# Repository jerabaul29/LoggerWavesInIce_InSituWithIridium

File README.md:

### NOTE - the content of this repository is kept available for archive, but we have a better instrument design released in 2021, see: https://github.com/jerabaul29/OpenMetBuoy-v2021a .

# Logger waves in ice with solar panel and Iridium communications

This is the repository for the 'waves in ice' instrument developed in this work:

```
An open source, versatile, affordable waves in ice instrument for scientific measurements in the Polar Regions
Jean Rabault, Graig Sutherland, Olav Gundersen, Atle Jensen, Aleksey Marchenko, Øyvind Breivik
```

https://www.sciencedirect.com/science/article/pii/S0165232X19300230

(preprint available here: https://arxiv.org/pdf/1901.02410.pdf ).

## Content of the repository

- **PCB_electronics**: details about the electronics boards.
- **DevelopmentCode**: code for the different components of the loggers.
- **ElectronicsList**: some bookkeeping of which components I need to buy to assemble. May be outdated.
- **SeedOPL**: the Seeed studios standard library. Could be used for putting the components on PCB from factory, not used now.

Quite a lot of cleaning and more detailed readmes is needed. This will happen as time goes and new series of instruments get built. If you have any questions, open an issue and / or feel free to contact me at ```jean.rblt@gmail.com```.

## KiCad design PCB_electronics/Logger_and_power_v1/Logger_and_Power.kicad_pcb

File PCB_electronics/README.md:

PCB files. The software used for developing this is the Open Source KiCAD.

Most advanced PCB is in **Logger_and_power_v1**.

Production was made through Seeed.

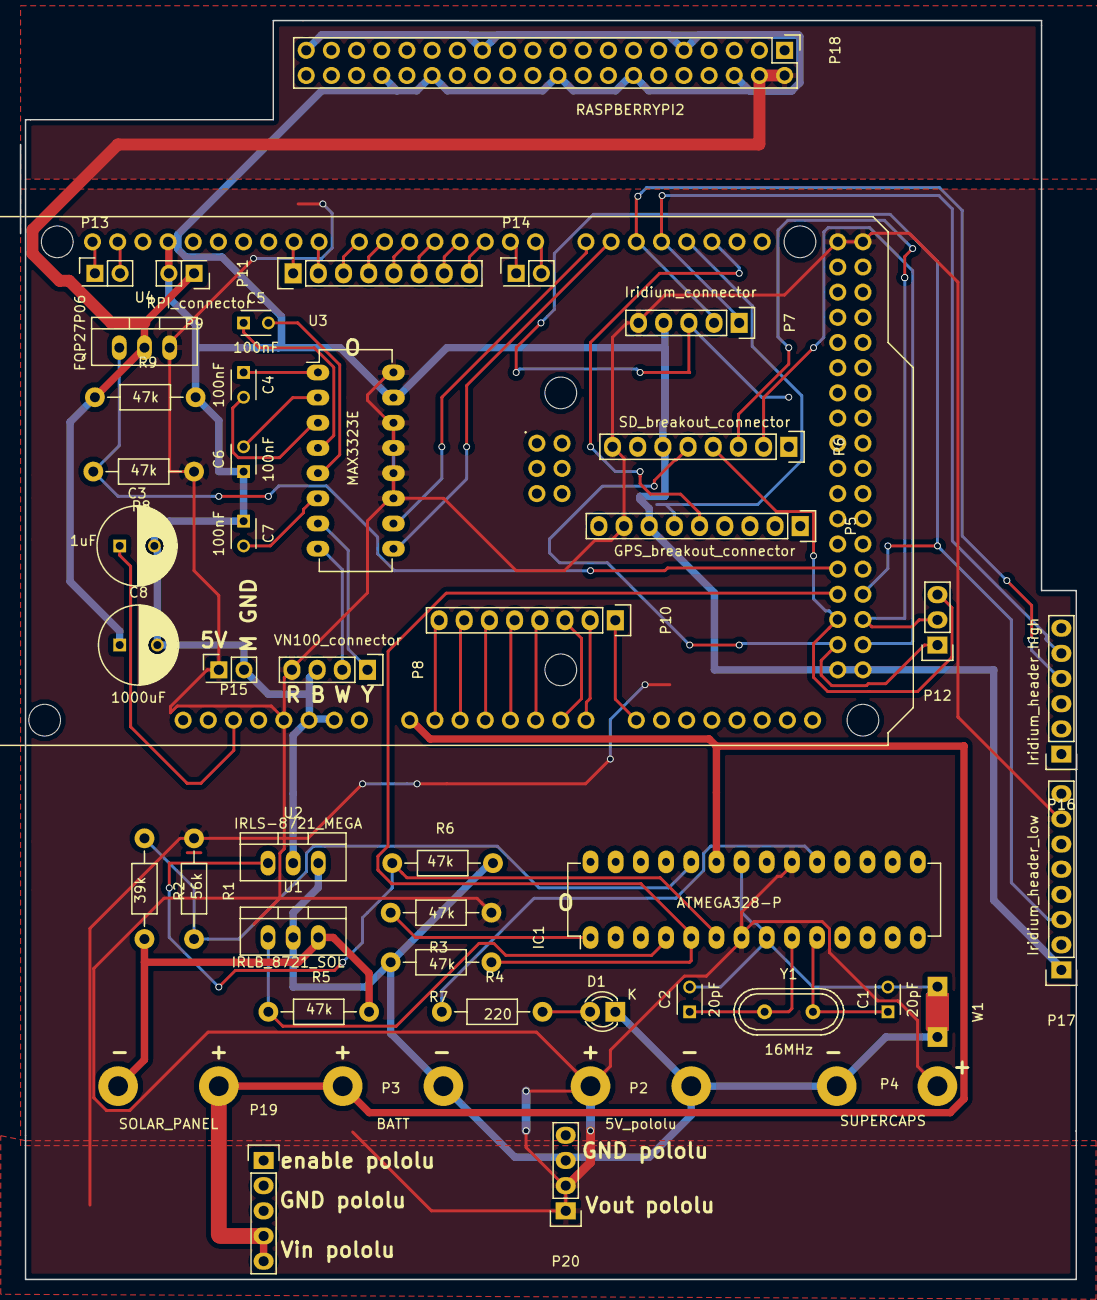
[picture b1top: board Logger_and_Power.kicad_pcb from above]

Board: 2 copper layers, 106.5 x 127.0 mm, 46 parts (1 on the bottom side), 57 nets.

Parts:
C1, C2: 20pF; C_Disc_D3_P2.5
C3: 1uF; C_Radial_D8_L11.5_P3.5
C4, C5, C6, C7: 100nF; C_Disc_D3_P2.5
C8: 1000uF; C_Radial_D8_L13_P3.8
D1: LED; LED-3MM
IC1: ATMEGA328-P; DIP-28_W7.62mm_LongPads
P1: SOLAR_PANEL; WireConnection_2.00mmDrill
P2: 5V_pololu; WireConnection_2.00mmDrill
P3: BATT; WireConnection_2.00mmDrill
P4: SUPERCAPS; WireConnection_2.00mmDrill
P5: GPS_breakout_connector; Pin_Header_Straight_1x09
P6: SD_breakout_connector; Pin_Header_Straight_1x08
P7: Iridium_connector; Pin_Header_Straight_1x05
P8: VN100_connector; Pin_Header_Straight_1x04
P9: RPI_connector; Pin_Header_Straight_2x01
P10, P11: CONN_01X08; Pin_Header_Straight_1x08
P12: CONN_01X03; Pin_Header_Straight_1x03
P13, P14, P15: CONN_01X02; Pin_Header_Straight_2x01
P16: Iridium_header_high; Pin_Header_Straight_1x06
P17: Iridium_header_low; Pin_Header_Straight_1x08
P18: RASPBERRYPI2; Pin_Header_Straight_2x20
P19: header_pololu_in; Pin_Header_Straight_1x05
P20: header_pololu_out; Pin_Header_Straight_1x04
R1: 56k; Resistor_Horizontal_RM10mm
R2: 39k; Resistor_Horizontal_RM10mm
R3, R5, R6, R7, R8, R9: 47k; Resistor_Horizontal_RM10mm
R4: 220; Resistor_Horizontal_RM10mm
U1: IRLB_8721_SOL; TO-220_Neutral123_Vertical
U2: IRLS-8721_MEGA; TO-220_Neutral123_Vertical
U3: MAX3323E; DIP-16_W7.62mm_LongPads
U4: FQP27P06; TO-220_Neutral123_Vertical
W1: NET-TIE; NetTie-I_Connected
XA1: Arduino_Mega2560_Shield
Y1: 16MHz; Crystal_HC49-U_Vertical

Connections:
+5V: IC1.7, IC1.20, P2.1, P4.1, P5.8, P6.8, P7.5, P8.4, P15.1, P17.7, P20.1, P20.2, R1.1, R3.1, R8.1, U3.11, U3.12, U3.13, U3.14, U3.16, U4.3, XA1.5V1, XA1.5V3, XA1.5V4
/Logger_part/ANALOG_1: P10.1, XA1.A8
/Logger_part/ANALOG_2: P10.2, XA1.A7
/Logger_part/ANALOG_3: P10.3, XA1.A6
/Logger_part/ANALOG_4: P10.4, XA1.A5
/Logger_part/ANALOG_5: P10.5, XA1.A4
/Logger_part/ANALOG_6: P10.6, XA1.A3
/Logger_part/ANALOG_7: P10.7, XA1.A2
/Logger_part/ANALOG_8: P10.8, XA1.A1
/Logger_part/DGTL_1: P11.1, XA1.D9
/Logger_part/DGTL_2: P11.2, XA1.D8
/Logger_part/DGTL_3: P11.3, XA1.D7
/Logger_part/DGTL_4: P11.4, XA1.D6
/Logger_part/DGTL_5: P11.5, XA1.D5
/Logger_part/DGTL_6: P11.6, XA1.D4
/Logger_part/DGTL_7: P11.7, XA1.D3
/Logger_part/DGTL_8: P11.8, XA1.D2
/Logger_part/IRD_ON_OFF: P7.3, P17.3, XA1.D49
/Logger_part/IRD_RXC: P7.1, P16.5, XA1.D17
/Logger_part/IRD_TXD: P7.2, P16.4, XA1.D16
/Logger_part/MEGA_RX_1: P5.5, XA1.D19
/Logger_part/MEGA_TX_1: P5.6, XA1.D18
/Logger_part/MISO: P6.4, P12.3, XA1.D50
/Logger_part/MOSI: P6.3, P12.2, XA1.D51
/Logger_part/RPI_control: R8.2, U4.1, XA1.D46
/Logger_part/RPI_header/RPI_power_5V: C8.1, P9.1, P18.2, P18.4, R9.1, U4.2
/Logger_part/RX0: P14.2, XA1.D0
/Logger_part/RX3: U3.9, XA1.D15
/Logger_part/SCK: P6.5, P12.1, XA1.D52
/Logger_part/SCL: P13.1, XA1.SCL
/Logger_part/SDA: P13.2, XA1.SDA
/Logger_part/SS: P6.2, XA1.D53
/Logger_part/TX0: P14.1, XA1.D1
/Logger_part/TX3: U3.10, XA1.D14
/Logger_part/VN_WHITE: P8.2, U3.8
/Logger_part/VN_YELLOW: P8.1, U3.7
/Power_part/A1: IC1.24, R1.2, R2.1
/Power_part/Batt_plus: IC1.23, P1.1, P3.1, P19.4, P19.5, XA1.A0
/Power_part/D3: IC1.4, R5.1, U1.1
/Power_part/D5: IC1.6, R6.1, U2.1
/Power_part/Feedback_Mega: IC1.5, R7.1, XA1.D48
/Power_part/MSFT_SOLAR_S: P1.2, R2.2, R5.2, U1.3
/Power_part/Mega_ground: C3.2, C6.1, C7.1, C8.2, P5.7, P6.6, P7.4, P8.3, P9.2, P15.2, P17.1, P18.6, P18.9, P18.14, P18.20, P18.25, P18.30, P18.34, P18.39, R9.2, U2.2, U3.15, XA1.GND1, XA1.GND2, XA1.GND3, XA1.GND5, XA1.GND6
/Power_part/Ref_gnd: C1.2, C2.2, IC1.8, IC1.22, W1.2
GND: D1.1, P2.2, P3.2, P4.2, P19.2, P19.3, P20.3, P20.4, R6.2, R7.2, U1.2, U2.3, W1.1
unnamed: C1.1, IC1.10, Y1.2
unnamed: C2.1, IC1.9, Y1.1
unnamed: C3.1, XA1.RST1
unnamed: C4.1, U3.1
unnamed: C4.2, U3.3
unnamed: C5.1, U3.4
unnamed: C5.2, U3.5
unnamed: C6.2, U3.2
unnamed: C7.2, U3.6
unnamed: D1.2, R4.2
unnamed: IC1.1, R3.2
unnamed: IC1.19, R4.1

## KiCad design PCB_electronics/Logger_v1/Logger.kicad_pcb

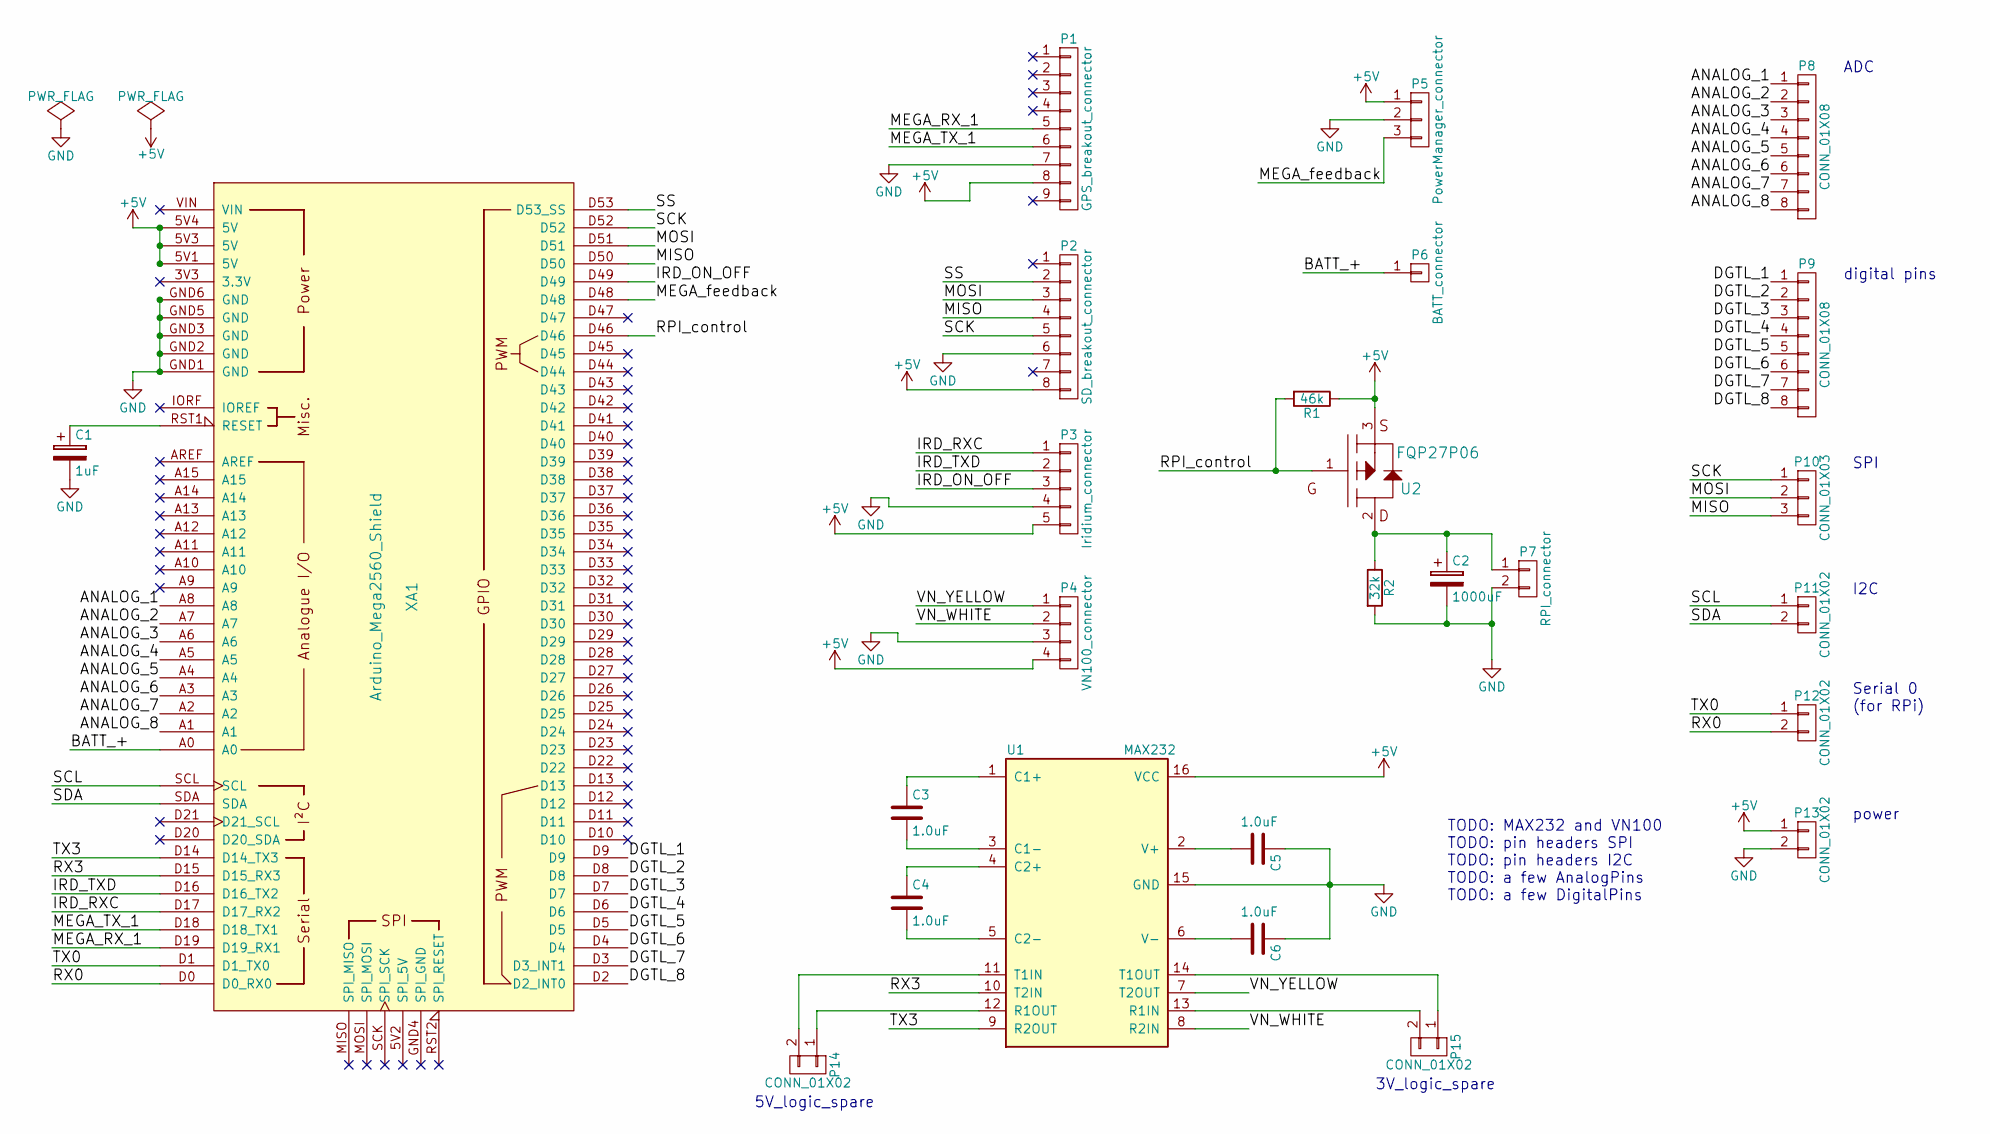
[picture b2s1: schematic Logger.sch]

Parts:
C1: 1uF; C_Disc_D3_P2.5
C2: 1000uF; C_Disc_D3_P2.5
C3, C4, C5, C6: 1.0uF
P1: GPS_breakout_connector
P2: SD_breakout_connector
P3: Iridium_connector
P4: VN100_connector
P5: PowerManager_connector
P6: BATT_connector
P7: RPI_connector
P8, P9: CONN_01X08
P10: CONN_01X03
P11, P12, P13, P14, P15: CONN_01X02
R1: 46k
R2: 32k
U1: MAX232
U2: FQP27P06
XA1: Arduino_Mega2560_Shield

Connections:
+5V: P1.8, P2.8, P3.5, P4.4, P5.1, P13.1, R1.1, U1.16 (VCC), U2.3, XA1.5V1 (5V), XA1.5V3 (5V), XA1.5V4 (5V); also elsewhere on the board
/ANALOG_1: P8.1, XA1.A8; also elsewhere on the board
/ANALOG_2: P8.2, XA1.A7; also elsewhere on the board
/ANALOG_3: P8.3, XA1.A6; also elsewhere on the board
/ANALOG_4: P8.4, XA1.A5; also elsewhere on the board
/ANALOG_5: P8.5, XA1.A4; also elsewhere on the board
/ANALOG_6: P8.6, XA1.A3; also elsewhere on the board
/ANALOG_7: P8.7, XA1.A2; also elsewhere on the board
/ANALOG_8: P8.8, XA1.A1; also elsewhere on the board
/BATT_+: P6.1, XA1.A0; also elsewhere on the board
/DGTL_1: P9.1, XA1.D9; also elsewhere on the board
/DGTL_2: P9.2, XA1.D8; also elsewhere on the board
/DGTL_3: P9.3, XA1.D7; also elsewhere on the board
/DGTL_4: P9.4, XA1.D6; also elsewhere on the board
/DGTL_5: P9.5, XA1.D5; also elsewhere on the board
/DGTL_6: P9.6, XA1.D4; also elsewhere on the board
/DGTL_7: P9.7, XA1.D3 (D3_INT1); also elsewhere on the board
/DGTL_8: P9.8, XA1.D2 (D2_INT0); also elsewhere on the board
/IRD_ON_OFF: P3.3, XA1.D49; also elsewhere on the board
/IRD_RXC: P3.1, XA1.D17 (D17_RX2); also elsewhere on the board
/IRD_TXD: P3.2, XA1.D16 (D16_TX2); also elsewhere on the board
/MEGA_RX_1: P1.5, XA1.D19 (D19_RX1); also elsewhere on the board
/MEGA_TX_1: P1.6, XA1.D18 (D18_TX1); also elsewhere on the board
/MEGA_feedback: P5.3, XA1.D48; also elsewhere on the board
/MISO: P2.4, P10.3, XA1.D50; also elsewhere on the board
/MOSI: P2.3, P10.2, XA1.D51; also elsewhere on the board
/RPI_control: R1.2, U2.1, XA1.D46; also elsewhere on the board
/RX0: P12.2, XA1.D0 (D0_RX0); also elsewhere on the board
/SCK: P2.5, P10.1, XA1.D52; also elsewhere on the board
/SCL: P11.1, XA1.SCL; also elsewhere on the board
/SDA: P11.2, XA1.SDA; also elsewhere on the board
/SS: P2.2, XA1.D53 (D53_SS); also elsewhere on the board
/TX0: P12.1, XA1.D1 (D1_TX0); also elsewhere on the board
/VN_WHITE: P4.2, U1.8 (R2IN)
/VN_YELLOW: P4.1, U1.7 (T2OUT)
GND: C1.2, C2.2, C5.1, C6.1, P1.7, P2.6, P3.4, P4.3, P5.2, P7.2, P13.2, R2.2, U1.15 (GND), XA1.GND1 (GND), XA1.GND2 (GND), XA1.GND3 (GND), XA1.GND5 (GND), XA1.GND6 (GND); also elsewhere on the board
unnamed 36: C1.1, XA1.RST1 (RESET); also elsewhere on the board
unnamed: C2.1, P7.1, R2.1, U2.2
unnamed: C3.1, U1.1 (C1+)
unnamed: C3.2, U1.3 (C1-)
unnamed: C4.1, U1.4 (C2+)
unnamed: C4.2, U1.5 (C2-)
unnamed: C5.2, U1.2 (V+)
unnamed: C6.2, U1.6 (V-)
unnamed: P14.1, U1.12 (R1OUT)
unnamed: P14.2, U1.11 (T1IN)
unnamed: P15.1, U1.14 (T1OUT)
unnamed: P15.2, U1.13 (R1IN)
unnamed 55: XA1.3V3 (3.3V); also elsewhere on the board
unnamed 56: XA1.5V2 (SPI_5V); also elsewhere on the board
unnamed 57: XA1.A9; also elsewhere on the board
unnamed 58: XA1.A10; also elsewhere on the board
unnamed 59: XA1.A11; also elsewhere on the board
unnamed 60: XA1.A12; also elsewhere on the board
unnamed 61: XA1.A13; also elsewhere on the board
unnamed 62: XA1.A14; also elsewhere on the board
unnamed 63: XA1.A15; also elsewhere on the board
unnamed 64: XA1.AREF; also elsewhere on the board
unnamed 65: XA1.D10; also elsewhere on the board
unnamed 66: XA1.D11; also elsewhere on the board
unnamed 67: XA1.D12; also elsewhere on the board
unnamed 68: XA1.D13; also elsewhere on the board
unnamed 69: XA1.D20 (D20_SDA); also elsewhere on the board
unnamed 70: XA1.D21 (D21_SCL); also elsewhere on the board
unnamed 71: XA1.D22; also elsewhere on the board
unnamed 72: XA1.D23; also elsewhere on the board
unnamed 73: XA1.D24; also elsewhere on the board
unnamed 74: XA1.D25; also elsewhere on the board
unnamed 75: XA1.D26; also elsewhere on the board
unnamed 76: XA1.D27; also elsewhere on the board
unnamed 77: XA1.D28; also elsewhere on the board
unnamed 78: XA1.D29; also elsewhere on the board
unnamed 79: XA1.D30; also elsewhere on the board
unnamed 80: XA1.D31; also elsewhere on the board
unnamed 81: XA1.D32; also elsewhere on the board
unnamed 82: XA1.D33; also elsewhere on the board
unnamed 83: XA1.D34; also elsewhere on the board
unnamed 84: XA1.D35; also elsewhere on the board
unnamed 85: XA1.D36; also elsewhere on the board
unnamed 86: XA1.D37; also elsewhere on the board
unnamed 87: XA1.D38; also elsewhere on the board
unnamed 88: XA1.D39; also elsewhere on the board
unnamed 89: XA1.D40; also elsewhere on the board
unnamed 90: XA1.D41; also elsewhere on the board
unnamed 91: XA1.D42; also elsewhere on the board
unnamed 92: XA1.D43; also elsewhere on the board
unnamed 93: XA1.D44; also elsewhere on the board
unnamed 94: XA1.D45; also elsewhere on the board
unnamed 95: XA1.D47; also elsewhere on the board
unnamed 96: XA1.GND4 (SPI_GND); also elsewhere on the board
unnamed 97: XA1.IORF (IOREF); also elsewhere on the board
unnamed 98: XA1.MISO (SPI_MISO); also elsewhere on the board
unnamed 99: XA1.MOSI (SPI_MOSI); also elsewhere on the board
unnamed 100: XA1.RST2 (SPI_RESET); also elsewhere on the board
unnamed 101: XA1.SCK (SPI_SCK); also elsewhere on the board
unnamed 102: XA1.VIN; also elsewhere on the board

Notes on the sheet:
TODO: MAX232 and VN100 TODO: pin headers SPI TODO: pin headers I2C TODO: a few AnalogPins TODO: a few DigitalPins
digital pins
ADC
SPI
I2C
power
Serial 0 (for RPi)
5V_logic_spare
3V_logic_spare

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
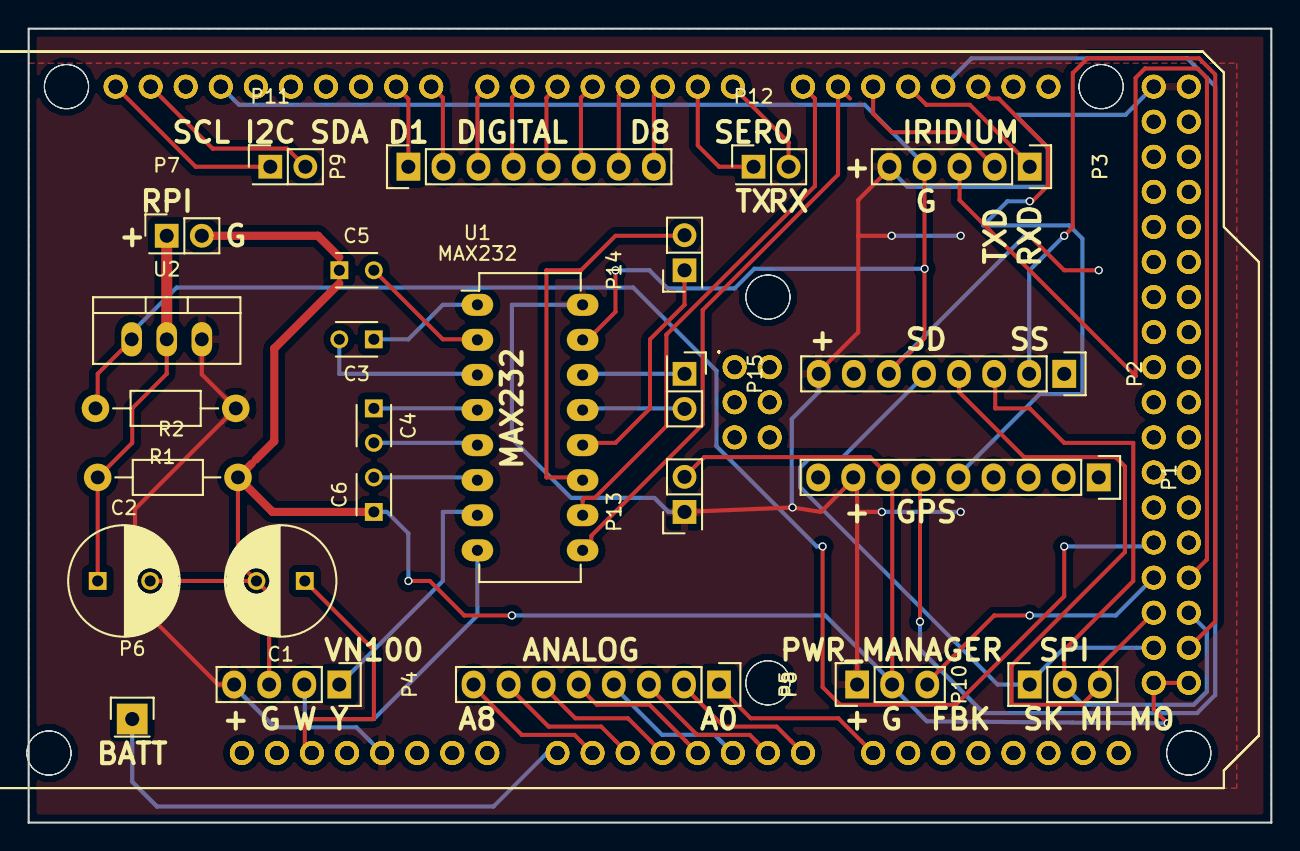
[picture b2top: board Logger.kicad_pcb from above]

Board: 2 copper layers, 90.0 x 57.5 mm, 27 parts (0 on the bottom side), 98 nets.

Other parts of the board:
XA1#2: Arduino_Mega2560_Shield

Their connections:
+5V: XA1#2.5V1, XA1#2.5V3, XA1#2.5V4; also elsewhere on the board
/ANALOG_1: XA1#2.A8; also elsewhere on the board
/ANALOG_2: XA1#2.A7; also elsewhere on the board
/ANALOG_3: XA1#2.A6; also elsewhere on the board
/ANALOG_4: XA1#2.A5; also elsewhere on the board
/ANALOG_5: XA1#2.A4; also elsewhere on the board
/ANALOG_6: XA1#2.A3; also elsewhere on the board
/ANALOG_7: XA1#2.A2; also elsewhere on the board
/ANALOG_8: XA1#2.A1; also elsewhere on the board
/BATT_+: XA1#2.A0; also elsewhere on the board
/DGTL_1: XA1#2.D9; also elsewhere on the board
/DGTL_2: XA1#2.D8; also elsewhere on the board
/DGTL_3: XA1#2.D7; also elsewhere on the board
/DGTL_4: XA1#2.D6; also elsewhere on the board
/DGTL_5: XA1#2.D5; also elsewhere on the board
/DGTL_6: XA1#2.D4; also elsewhere on the board
/DGTL_7: XA1#2.D3; also elsewhere on the board
/DGTL_8: XA1#2.D2; also elsewhere on the board
/IRD_ON_OFF: XA1#2.D49; also elsewhere on the board
/IRD_RXC: XA1#2.D17; also elsewhere on the board
/IRD_TXD: XA1#2.D16; also elsewhere on the board
/MEGA_RX_1: XA1#2.D19; also elsewhere on the board
/MEGA_TX_1: XA1#2.D18; also elsewhere on the board
/MEGA_feedback: XA1#2.D48; also elsewhere on the board
/MISO: XA1#2.D50; also elsewhere on the board
/MOSI: XA1#2.D51; also elsewhere on the board
/RPI_control: XA1#2.D46; also elsewhere on the board
/RX0: XA1#2.D0; also elsewhere on the board
/SCK: XA1#2.D52; also elsewhere on the board
/SCL: XA1#2.SCL; also elsewhere on the board
/SDA: XA1#2.SDA; also elsewhere on the board
/SS: XA1#2.D53; also elsewhere on the board
/TX0: XA1#2.D1; also elsewhere on the board
GND: XA1#2.GND1, XA1#2.GND2, XA1#2.GND3, XA1#2.GND5, XA1#2.GND6; also elsewhere on the board
unnamed 36: XA1#2.RST1; also elsewhere on the board
unnamed 55: XA1#2.3V3; also elsewhere on the board
unnamed 56: XA1#2.5V2; also elsewhere on the board
unnamed 57: XA1#2.A9; also elsewhere on the board
unnamed 58: XA1#2.A10; also elsewhere on the board
unnamed 59: XA1#2.A11; also elsewhere on the board
unnamed 60: XA1#2.A12; also elsewhere on the board
unnamed 61: XA1#2.A13; also elsewhere on the board
unnamed 62: XA1#2.A14; also elsewhere on the board
unnamed 63: XA1#2.A15; also elsewhere on the board
unnamed 64: XA1#2.AREF; also elsewhere on the board
unnamed 65: XA1#2.D10; also elsewhere on the board
unnamed 66: XA1#2.D11; also elsewhere on the board
unnamed 67: XA1#2.D12; also elsewhere on the board
unnamed 68: XA1#2.D13; also elsewhere on the board
unnamed 69: XA1#2.D20; also elsewhere on the board
unnamed 70: XA1#2.D21; also elsewhere on the board
unnamed 71: XA1#2.D22; also elsewhere on the board
unnamed 72: XA1#2.D23; also elsewhere on the board
unnamed 73: XA1#2.D24; also elsewhere on the board
unnamed 74: XA1#2.D25; also elsewhere on the board
unnamed 75: XA1#2.D26; also elsewhere on the board
unnamed 76: XA1#2.D27; also elsewhere on the board
unnamed 77: XA1#2.D28; also elsewhere on the board
unnamed 78: XA1#2.D29; also elsewhere on the board
unnamed 79: XA1#2.D30; also elsewhere on the board
unnamed 80: XA1#2.D31; also elsewhere on the board
unnamed 81: XA1#2.D32; also elsewhere on the board
unnamed 82: XA1#2.D33; also elsewhere on the board
unnamed 83: XA1#2.D34; also elsewhere on the board
unnamed 84: XA1#2.D35; also elsewhere on the board
unnamed 85: XA1#2.D36; also elsewhere on the board
unnamed 86: XA1#2.D37; also elsewhere on the board
unnamed 87: XA1#2.D38; also elsewhere on the board
unnamed 88: XA1#2.D39; also elsewhere on the board
unnamed 89: XA1#2.D40; also elsewhere on the board
unnamed 90: XA1#2.D41; also elsewhere on the board
unnamed 91: XA1#2.D42; also elsewhere on the board
unnamed 92: XA1#2.D43; also elsewhere on the board
unnamed 93: XA1#2.D44; also elsewhere on the board
unnamed 94: XA1#2.D45; also elsewhere on the board
unnamed 95: XA1#2.D47; also elsewhere on the board
unnamed 96: XA1#2.GND4; also elsewhere on the board
unnamed 97: XA1#2.IORF; also elsewhere on the board
unnamed 98: XA1#2.MISO; also elsewhere on the board
unnamed 99: XA1#2.MOSI; also elsewhere on the board
unnamed 100: XA1#2.RST2; also elsewhere on the board
unnamed 101: XA1#2.SCK; also elsewhere on the board
unnamed 102: XA1#2.VIN; also elsewhere on the board

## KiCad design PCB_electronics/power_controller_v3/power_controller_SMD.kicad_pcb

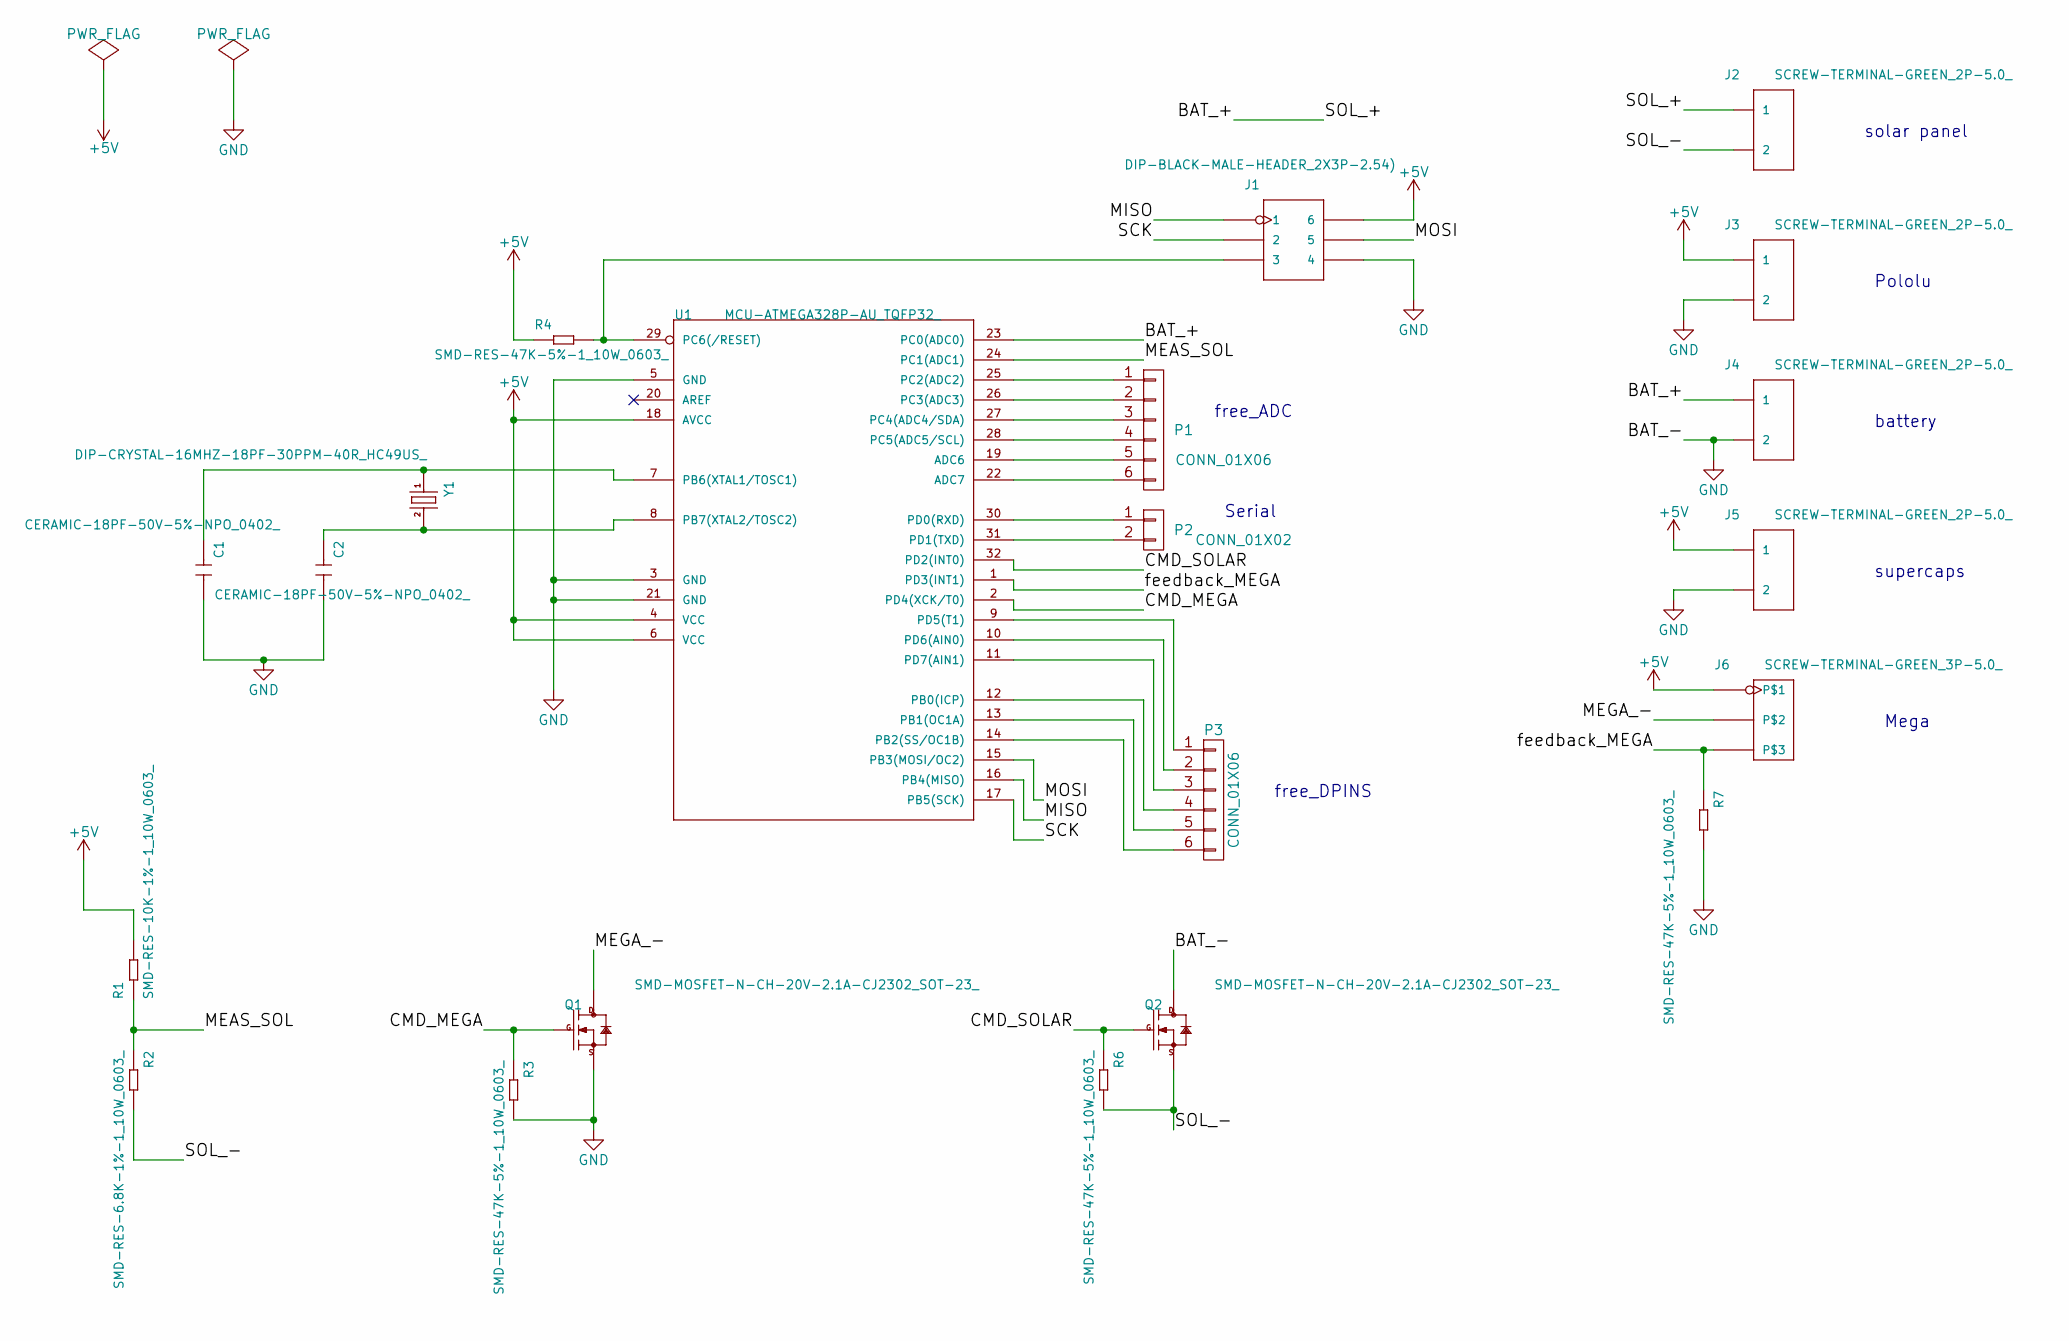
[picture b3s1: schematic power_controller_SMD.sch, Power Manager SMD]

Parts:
C1, C2: CERAMIC-18PF-50V-5%-NPO_0402_; C0402; MPN CC0402JRNPO9BN180
J1: DIP-BLACK-MALE-HEADER_2X3P-2.54); H2X3-2.54; MPN P125-12A1BS116A1
J2, J3, J4, J5: SCREW-TERMINAL-GREEN_2P-5.0_; H2-5.0-10.5X8.0MM
J6: SCREW-TERMINAL-GREEN_3P-5.0_; H3-5.0-15.5X8.0MM
P1, P3: CONN_01X06; Pin_Header_Straight_1x06
P2: CONN_01X02; Pin_Header_Straight_1x02
Q1, Q2: SMD-MOSFET-N-CH-20V-2.1A-CJ2302_SOT-23_; SOT-23; MPN CJ2302
R1: SMD-RES-10K-1%-1_10W_0603_; R0603; MPN RC0603FR-0710KL
R2: SMD-RES-6.8K-1%-1_10W_0603_; R0603; MPN RC0805JR-07220KL
R3, R4, R6, R7: SMD-RES-47K-5%-1_10W_0603_; R0603; MPN RC0603JR-0747KL
U1: MCU-ATMEGA328P-AU_TQFP32_; TQFP32-0.8-7X7MM; MPN ATMEGA328P-AU
Y1: DIP-CRYSTAL-16MHZ-18PF-30PPM-40R_HC49US_; HC49US; MPN HC-49US 16.000MHz

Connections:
+5V: J1.6, J3.1, J5.1, J6.1, R1.2, R4.1, U1.4 (VCC), U1.6 (VCC), U1.18 (AVCC)
/BAT_+: J2.1, J4.1, U1.23 (PC0(ADC0))
/CMD_MEGA: Q1.1 (G), R3.1, U1.2 (PD4(XCK/T0))
/CMD_SOLAR: Q2.1 (G), R6.1, U1.32 (PD2(INT0))
/MEAS_SOL: R1.1, R2.1, U1.24 (PC1(ADC1))
/MEGA_-: J6.2, Q1.3 (D)
/MISO: J1.1, U1.16 (PB4(MISO))
/MOSI: J1.5, U1.15 (PB3(MOSI/OC2))
/SCK: J1.2, U1.17 (PB5(SCK))
/SOL_-: J2.2, Q2.2 (S), R2.2, R6.2
/feedback_MEGA: J6.3, R7.1, U1.1 (PD3(INT1))
GND: C1.2, C2.2, J1.4, J3.2, J4.2, J5.2, Q1.2 (S), Q2.3 (D), R3.2, R7.2, U1.3 (GND), U1.5 (GND), U1.21 (GND)
unnamed: C1.1, U1.7 (PB6(XTAL1/TOSC1)), Y1.1
unnamed: C2.1, U1.8 (PB7(XTAL2/TOSC2)), Y1.2
unnamed: J1.3, R4.2, U1.29 (PC6(/RESET))
unnamed: P1.1, U1.25 (PC2(ADC2))
unnamed: P1.2, U1.26 (PC3(ADC3))
unnamed: P1.3, U1.27 (PC4(ADC4/SDA))
unnamed: P1.4, U1.28 (PC5(ADC5/SCL))
unnamed: P1.5, U1.19 (ADC6)
unnamed: P1.6, U1.22 (ADC7)
unnamed: P2.1, U1.30 (PD0(RXD))
unnamed: P2.2, U1.31 (PD1(TXD))
unnamed: P3.1, U1.9 (PD5(T1))
unnamed: P3.2, U1.10 (PD6(AIN0))
unnamed: P3.3, U1.11 (PD7(AIN1))
unnamed: P3.4, U1.12 (PB0(ICP))
unnamed: P3.5, U1.13 (PB1(OC1A))
unnamed: P3.6, U1.14 (PB2(SS/OC1B))

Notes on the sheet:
solar panel
Pololu
battery
supercaps
Mega
Serial
free_ADC
free_DPINS

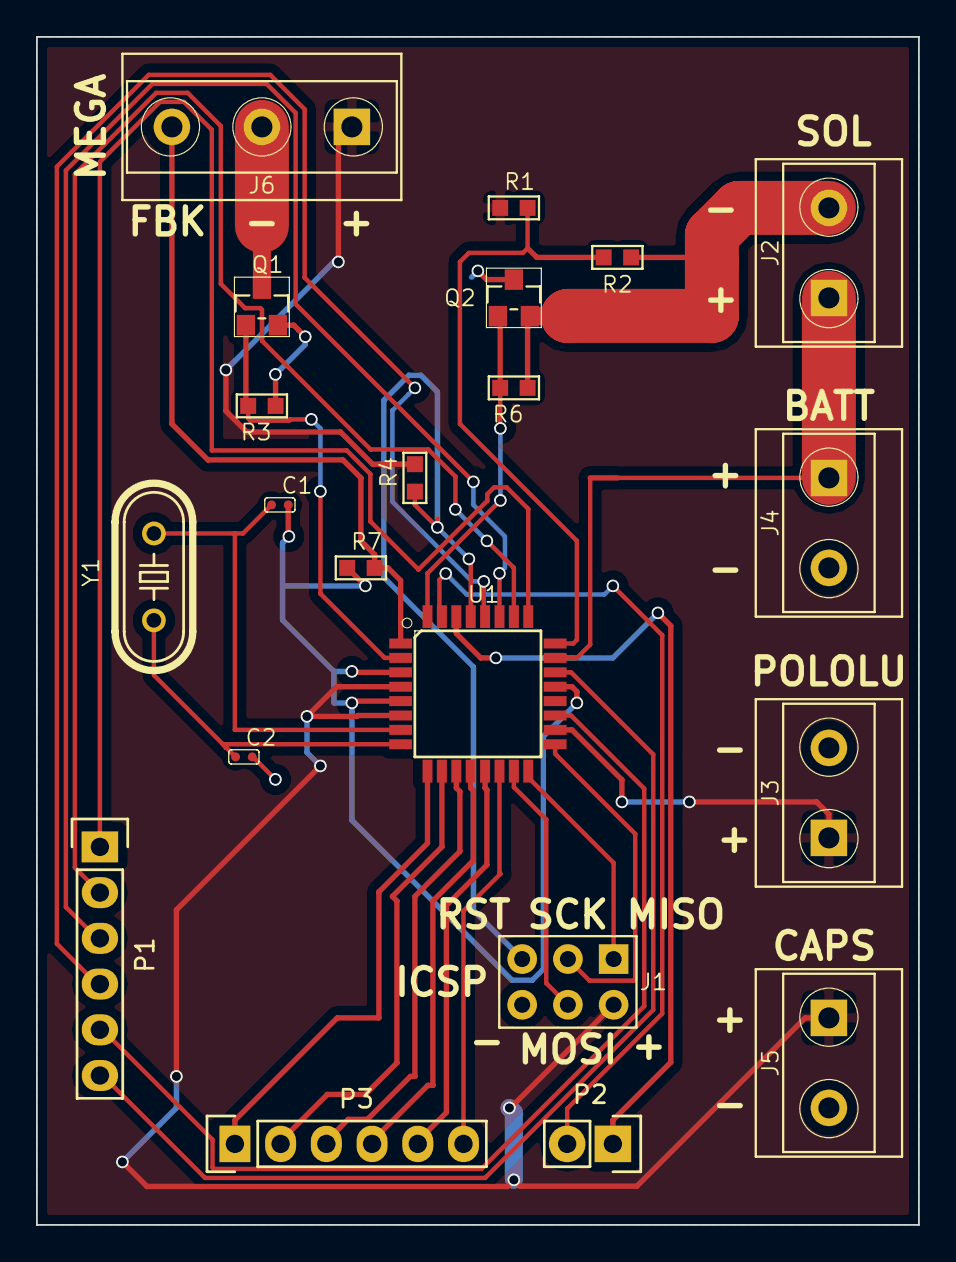
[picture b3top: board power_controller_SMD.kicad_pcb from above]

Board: 2 copper layers, 49.0 x 66.0 mm, 21 parts (0 on the bottom side), 29 nets.

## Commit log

2017-07-25 working PowerControl_FromScratch reading voltage panel and battery
2017-07-25 working solar power control with mega feedback and sleep; need to optimize sleeP (?)
2017-07-25 code ready for tests
2017-07-25 ready for a test
2017-07-26 added LED visual feedback
2017-07-27 added png material about power control system
2017-07-27 working on Arduino Mega logger
2017-07-27 thinking about how to add Iridium and RaspberryPi
2017-07-28 working on the Mega code
2017-07-28 added low battery threshold in PowerControl
2017-07-28 should have fixed the when mega up issue
2017-07-28 small improvement; Mega gets 2 seconds to decide if wants to boot or sleep
2017-07-28 done for today; logger test with older version of code (from before lunch) working ok but mega sleeping one too many cycle; should be fixed in present code
2017-07-31 working on the Iridium part
2017-07-31 ok Iridium string containing GPS information
2017-08-01 working Iridium transmissions
2017-08-01 added sending of Iridium vital sign to ArduinoMega
2017-08-01 receive and transmit with Iridium work
2017-08-01 working receive number of sleep cycles
2017-08-02 added Iridium feedback to Arduino Mega code; should set number of sleeps as EEPROM variable
2017-08-02 added number of sleeps update from Iridium in the Mega code
2017-08-03 working on RPi vs Logger communications
2017-08-03 updated Arduino Mega with RPI interaction; added script to be put in RPI crontab
2017-08-03 corrected error in RPi_Control; added Iridium guards in Mega code
2017-08-03 corrected a mistake in the ArduinoMega code (delay that forced 0 in MGA_FBK and Mega shutdown
2017-08-03 working now
2017-08-04 state of the code when doing test all except Iridium 04082017
2017-08-04 completed CHECKLIST: Arduino Mega EEPROM must be initialized with the right number of sleeps
2017-08-04 power working with no LED
2017-08-04 new test
2017-08-04 possibly corrected bug about how often Mega wakes up
2017-08-04 had forgotten to confirm on the RPi side when finished, added now; the bugs were due to Mega reset on opening of serial, not code
2017-08-15 parsing of Mega data works
2017-08-16 working on computing the statistics
2017-08-16 compute_statistics working fine
2017-08-16 save all to be transmitted as float16
2017-08-17 wrote the code to send RPi data through Iridium; to check!
2017-11-23 went again a bit through the code
2017-11-24 small additions in comment
2017-11-27 working on KiCAD
2017-11-28 first version of power controller
2017-11-28 some stupid changes
2017-11-28 correct new PSB with net-tie on master
2017-11-28 removed all files
2017-11-29 files to send to Olav for double checking
2017-11-30 added pdf prints for Olav
2017-12-12 v2 with DIL ATMega
2017-12-12 board v3 seems ok
2017-12-12 ready to generate first gerbers for test for power manager v3
2018-02-09 updated list components prototype
2018-02-19 compute statistics handling VN100 input plus added some directional calculations
2018-02-19 still testing dir spec
2018-02-20 some updates to compute_statistics
2018-02-21 updated compute statistics code
2018-02-21 updated comments and code in sleeping code of power controller
2018-02-21 cleaned / re commented the power manager code
2018-02-21 small things
2018-02-21 cleaning the code
2018-02-21 some updates to wave computation for dir moments
2018-02-22 some updates to wave calc
2018-02-23 finished wave computation + binary write/read
2018-02-23 cleaning code
2018-02-23 work on client_device
2018-02-23 written CDV class
2018-02-23 added checks on number of sleeps
2018-02-23 fully initialized object
2018-02-23 switched to mega device through CDV class
2018-02-23 not working
2018-02-23 cleaned the code for power manager
2018-02-23 ready for test of clean power manager
2018-02-23 updated binary write/read
2018-02-25 updating documentation
2018-02-25 modified sleep and watchdog to be a class
2018-02-25 refactoring
2018-02-26 cleaned up code
2018-02-26 ongoing work
2018-02-27 compiling with battery controller class
2018-02-27 working on refactoring
2018-02-27 working
2018-02-28 moving ArduinoMega to Platformio
2018-02-28 listing tasks todo
2018-02-28 building iridium manager
2018-02-28 working on code
2018-02-28 remains to implement: VN100 and RaspberryPi interaction
2018-03-01 ready for first tests of logging
2018-03-01 try to upload; not working yet
2018-03-01 corrected a mistake in sd manager
2018-03-01 moved some debug output to their functions
2018-03-01 renamed so that class and holding files have same names
2018-03-01 fixed compatibility bug with how VN100 data was posted for old parser to work
2018-03-01 now also timestamps work as they should
2018-03-01 iridium vital message is set ok
2018-03-06 debug macros working fine
2018-03-06 updating sd manager to support several types of files on Arduino SD card
2018-03-07 working on RaspberryManager
2018-03-12 RaspberryPi control code compiling
2018-03-12 problem in receiving from RPi
2018-03-12 everything should work now
2018-03-12 cosmetic changes to debugging messages
2018-03-12 corrected some format issues
2018-03-12 woring: get the I files on Mega SD card in debug mode
2018-03-13 made debugging better
2018-03-13 corrected a mistake in filename error
2018-03-13 fixed problem with bad data lines
2018-03-13 made the code easier to upload on the Pi
2018-03-13 probably a problem of watchdog reset when receiving data from RPi; should be corrected now
2018-03-13 small changes
2018-03-13 seems RPi wakeup from Mega not working
2018-03-13 read data line by line
2018-03-13 was missig a pinMode for controlling RPi
2018-03-13 was using wrong pin to power RPi on; corrected
2018-03-13 new full test
2018-03-13 this uploaded version worked
2018-03-14 set use iridium, corrected preprocessor typo
2018-03-14 this worked fine
2018-03-14 fix an issue with length of catched gprmc message
2018-03-14 added link to the commit that works before the strange reboot issue
2018-03-14 fixed problem with power manager
2018-03-14 testing on Iridium UiO test
2018-03-15 read data line by line. Shortens array if less than 24 minutes
2018-03-15 power controller should be ready for release
2018-03-15 logger in box working fine, but regularly strange 3500ms delays in logging of VN100
2018-03-15 should be the code used for tests the Thursday before leaving to Svalbard
2018-03-16 this is the code uploaded on Friday before going to Svalbard; the RPi code version is the one in the copy_code_RPI_working_but_slow_paging folder
2018-03-16 corrected small mistake on duration of sleep in power manager
2018-03-21 scripts to test reading and plotting Iridium messages
2018-03-21 working on code to process incoming data automatically
2018-03-21 working on automation
2018-03-21 working automatic data download from google and upload to github
2018-03-21 working on automatic processing of downloaded data
2018-03-22 automatic association is ok
2018-03-25 ready to test python automatic processing
2018-03-25 working non noise normalized spectrogram!
2018-03-25 working process code
2018-03-25 processing data works
2018-03-26 added denoising
2018-03-26 updated figures names to show if denoising
2018-04-11 nothing important
2018-05-04 working on kicad logger
2018-05-09 schematic logger seems ok
2018-05-09 placed components 1
2018-05-09 wired board ok
2018-05-09 corrected error on MAX232
2018-05-09 drc warning but should be ok
2018-05-09 extended slightly the board
2018-05-11 fixed interpolation for downsampling spectrum
2018-05-11 ordered first prototype logger shield
2018-05-16 updated data analysis code with directional spectrum and automated some part of paths
2018-05-16 cleaned a bit
2018-05-24 ready to make some tests with the new logger board
2018-05-25 just some small changes
2018-05-25 wrote class for high frequency exchanges to RPi
2018-05-25 working on faster data transfesr
2018-05-26 working on transmitting faster
2018-05-26 noise
2018-05-26 using the 'high speed' RPi USB manager; to test
2018-05-26 reduce duration of logging to 25 minutes
2018-05-26 working on the PCB
2018-05-26 routed ok
2018-05-26 all working; problem was being put in spam
2018-05-26 improved 5V plane
2018-05-26 last test of 260518
2018-05-26 doing tests now; resume tests tomorrow; if not working, increase back to 512 the size of the iridium buffer
2018-05-28 ready to try to shift the power controller
2018-05-28 moved more space for power controller
2018-05-28 retablished 512bytes rx buffers; new PCB with logger and power and headers
2018-05-28 corrected shape of the board; added missing wire
2018-06-07 fixed an issue in the raspberry pi control on the RPi
2018-08-01 small change
2018-08-02 some small changes; this is the version put in the loggers for Nansen project
2018-08-06 some updates to make ready automatic processing of Nansen data
2018-09-11 some small updates for being able to work on the Nansen legacy cruise data
2019-05-23 added simple BOM
2019-07-30 just some autosave
2019-07-30 now pololu on PCB; need to export gerbers still
2019-07-30 PCB with pololu support, for order 07-2019
2019-10-07 just commit to work further
2019-10-08 just recompiling the mega stuff
2019-10-08 working on the pcb v3.5
2019-10-09 now the v3.5 of the PCB: v3, integrated Pololu, with correct names on the PCB
2019-10-25 v3.6 with a bit more on the PCB silk mask
2019-10-25 minor stuff
2019-11-19 some additional infos
2019-12-19 a separate folder with the power controller in working version
2019-12-21 now working compilation with a small modif
2019-12-21 the hex files
2019-12-21 a few small fixes, now also the main ArduinoMega folder should compile with Arduino IDE
2020-02-19 a bit of cleaning old unused folders
2020-02-19 update readme with link to published manuscript
2020-02-20 attempt to solve a battery voltage readout issue
2020-06-17 Add user manual
2020-06-17 a few typos
2020-06-18 typo
2020-06-22 Add raw data extraction
